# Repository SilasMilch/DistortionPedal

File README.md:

DistortionPedal
Distortion Pedal PCB. Schematics are from WemplerPedal. Huge thanks to them!!!

Aktuelle Verbesserungs Ideen: Die Variablen Widerstände müssten noch benannt werden, mit ihrer Funktion. 
++ 2 Löcher hinzufügen für eine stanile Montierung des PCBs.

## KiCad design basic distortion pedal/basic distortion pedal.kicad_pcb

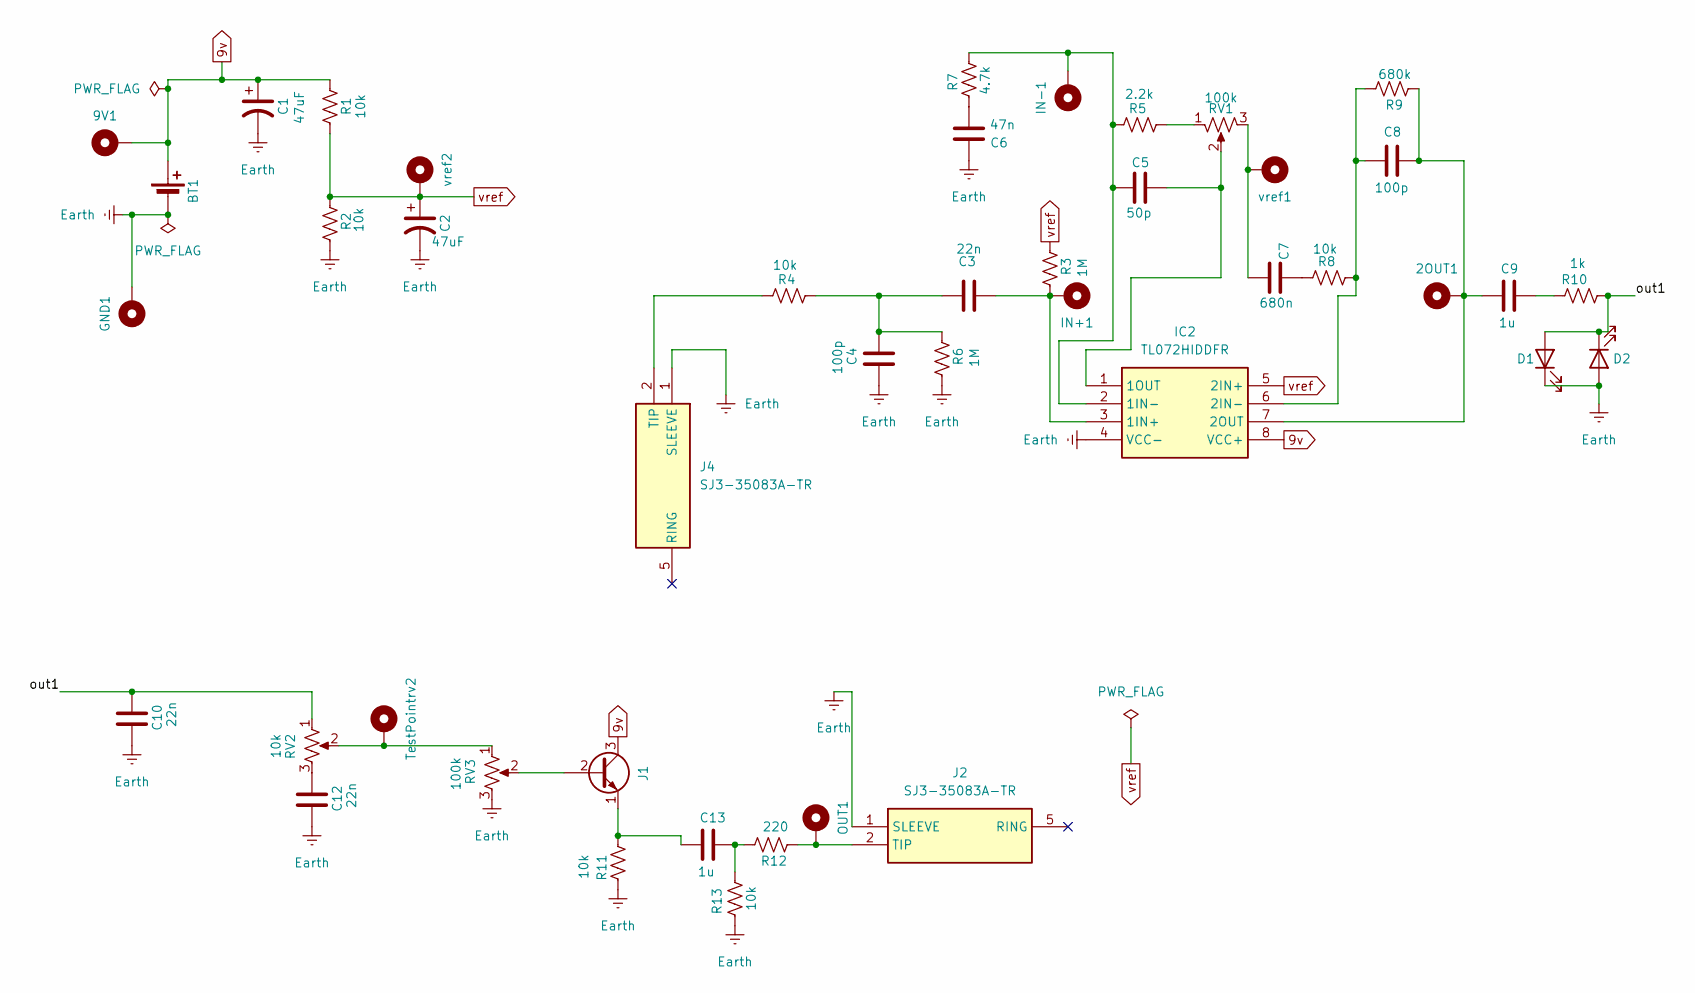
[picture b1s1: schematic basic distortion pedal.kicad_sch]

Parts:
2OUT1, 9V1: MountingHole_Pad; TestPoint_Pad_1.0x1.0mm
BT1: 9.6V; TerminalBlock_Altech_AK300-2_P5.00mm
C1, C2: 47uF; CP_Elec_6.3x5.8
C3, C10, C12: 22n; C_0201_0603Metric_Pad0.64x0.40mm_HandSolder
C4, C8: 100p; C_0201_0603Metric_Pad0.64x0.40mm_HandSolder
C5: 50p; C_0201_0603Metric_Pad0.64x0.40mm_HandSolder
C6: 47n; C_0201_0603Metric_Pad0.64x0.40mm_HandSolder
C7: 680n; C_0805_2012Metric_Pad1.18x1.45mm_HandSolder
C9, C13: 1u; C_01005_0402Metric_Pad0.57x0.30mm_HandSolder
D1, D2: LED; C4SMARGYCS4V1BB1
GND1: MountingHole_Pad; TestPoint_Pad_1.0x1.0mm
IC2: TL072HIDDFR; SOT65P280X110-8N; Mouser Part Number 595-TL072HIDDFR
IN+1: MountingHole_Pad; TestPoint_Pad_1.0x1.0mm
IN-1: MountingHole_Pad; TestPoint_Pad_1.0x1.0mm
J1: J201; TO-18-3
J2, J4: SJ3-35083A-TR; SJ335083ATR-SMALL; Mouser Part Number 179-SJ3-35083A-TR
OUT1: MountingHole_Pad; TestPoint_Pad_1.0x1.0mm
R1, R2, R4, R8, R11, R13: 10k; R_0805_2012Metric_Pad1.20x1.40mm_HandSolder
R3, R6: 1M; R_0805_2012Metric_Pad1.20x1.40mm_HandSolder
R5: 2.2k; R_0805_2012Metric_Pad1.20x1.40mm_HandSolder
R7: 4.7k; R_0805_2012Metric_Pad1.20x1.40mm_HandSolder
R9: 680k; R_0805_2012Metric_Pad1.20x1.40mm_HandSolder
R10: 1k; R_0805_2012Metric_Pad1.20x1.40mm_HandSolder
R12: 220; R_0805_2012Metric_Pad1.20x1.40mm_HandSolder
RV1, RV3: 100k; 51CADE24E20L-SMALL
RV2: 10k; 51CADE24E20L-SMALL
TestPointrv2: MountingHole_Pad; TestPoint_Pad_1.0x1.0mm
vref1, vref2: MountingHole_Pad; TestPoint_Pad_1.0x1.0mm

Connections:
9v: 9V1.1, BT1.1 (+), C1.1, IC2.8 (VCC+), J1.3 (C), R1.1
/out1: C10.1, D1.2 (A), D2.1 (K), R10.2, RV2.1
Earth: BT1.2 (-), C1.2, C2.2, C4.1, C6.2, C10.2, C12.2, D1.1 (K), D2.2 (A), GND1.1, IC2.4 (VCC-), J2.1 (SLEEVE), J4.1 (SLEEVE), R2.2, R6.2, R11.1, R13.2, RV3.3
unnamed: C3.1, C4.2, R4.2, R6.1
unnamed: C6.1, R7.1
unnamed: C7.1, RV1.3, vref1.1
unnamed: C7.2, R8.1
unnamed: C9.2, R10.1
unnamed: C12.1, RV2.3
unnamed: C13.2, R12.2, R13.1
unnamed: C3.2, IC2.3 (1IN+), IN+1.1, R3.2
unnamed: C5.1, IC2.2 (1IN-), IN-1.1, R5.1, R7.2
unnamed: C5.2, IC2.1 (1OUT), RV1.2
unnamed: C8.1, IC2.6 (2IN-), R8.2, R9.2
unnamed: 2OUT1.1, C8.2, C9.1, IC2.7 (2OUT), R9.1
unnamed: J1.2 (B), RV3.2
unnamed: C13.1, J1.1 (E), R11.2
unnamed: J2.2 (TIP), OUT1.1, R12.1
unnamed: J4.2 (TIP), R4.1
unnamed: R5.2, RV1.1
unnamed: RV2.2, RV3.1, TestPointrv2.1
vref: C2.1, IC2.5 (2IN+), R1.2, R2.1, R3.1, vref2.1

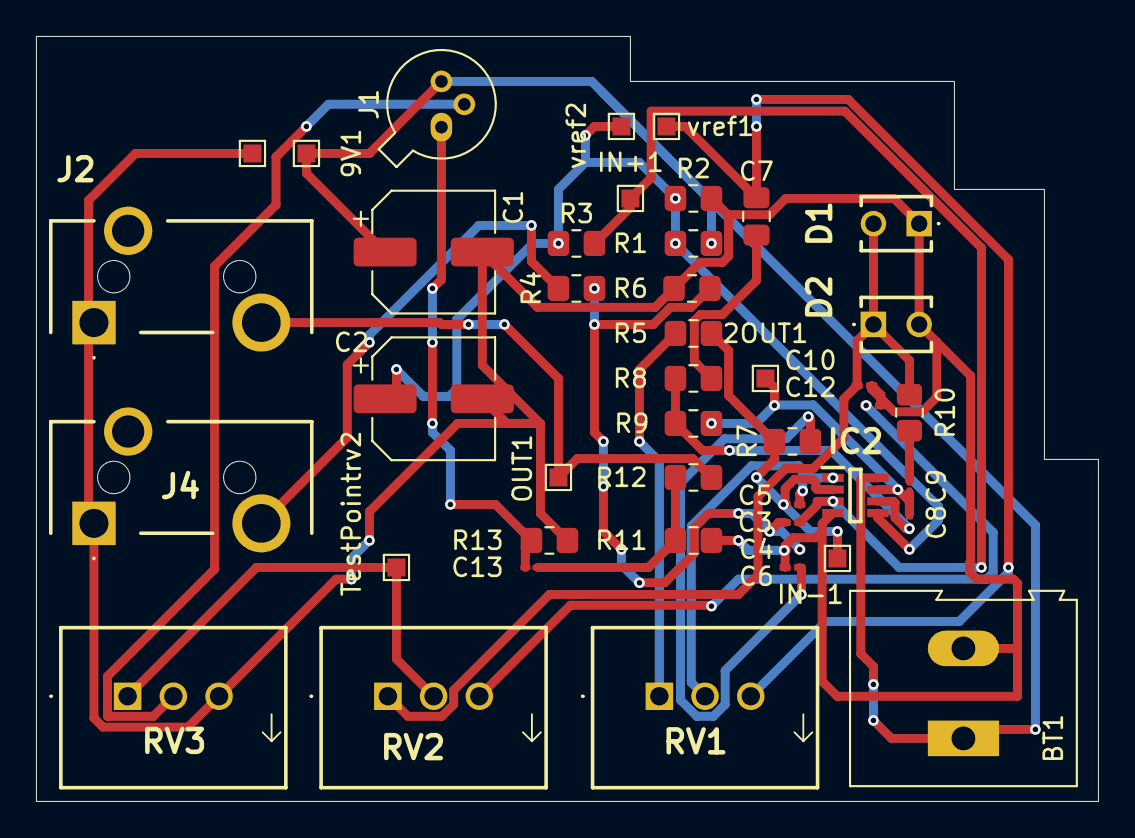
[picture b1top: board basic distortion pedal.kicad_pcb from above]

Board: 2 copper layers, 59.0 x 42.5 mm, 44 parts (0 on the bottom side), 22 nets.

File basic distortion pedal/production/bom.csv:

Designator,Footprint,Quantity,Value,LCSC Part #
BT1,TerminalBlock_Altech_AK300-2_P5.00mm,1,9.6V,
"C1, C2",CP_Elec_6.3x5.8,2,47uF,
"C10, C12, C3",0201,3,22n,
"C13, C9",01005,2,1u,
"C4, C8",0201,2,100p,
C5,0201,1,50p,
C6,0201,1,47n,
C7,0805,1,680n,
"D1, D2",C4SMARGYCS4V1BB1,2,LED,
IC2,SOT65P280X110-8N,1,TL072HIDDFR,
J1,TO-18-3,1,J201,
"J2, J4",SJ335083ATR-SMALL,2,SJ3-35083A-TR,
"R1, R11, R13, R2, R4, R8",0805,6,10k,
R10,0805,1,1k,
R12,0805,1,220,
"R3, R6",0805,2,1M,
R5,0805,1,2.2k,
R7,0805,1,4.7k,
R9,0805,1,680k,
"RV1, RV3",51CADE24E20L-SMALL,2,100k,
RV2,51CADE24E20L-SMALL,1,10k,

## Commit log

2025-02-21 Rename Pic2.jpg to Pic01.jpg
2025-02-21 Rename Pic1.jpg to Pic02.jpg
2025-02-22 README.md aktualisieren
2025-02-25 Rename basic_distortion_pedal_2025-02-25_15-47-04.zip to ??.md
